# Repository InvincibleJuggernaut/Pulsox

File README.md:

<h2>Introduction</h2>

<p> Pulse oximeters are electronic devices capable of measuring blood oxygen concentration levels as well as heart beat rate. Although they originally found their use only in medical institutions, the COVID-19 pandemic led to rise in demand for such devices. Naturally, prices shot up through the roof with people being forced to buy them at 3-4x the prices to save their dear ones' lives. </p>
<p> Pulsox is an IoT based pulse oximeter capable of detecting heart rate as well as oxygen concentration. The data is displayed locally in the LCD display as well as sent to the Blynk IoT platform. This data can be visualized in real-time through an app. 
  </p>

<h2>Installation</h2>

<p>Following are the steps related to usage and installation:</p>
<ul>
  <li>Once the circuit has been assembled with the <a href="https://github.com/InvincibleJuggernaut/Pulsox#components">components</a> as shown <a href="https://github.com/InvincibleJuggernaut/Pulsox#schematic">here</a>, connect the microcontroller to the PC using a USB cable.</li>
  <li>Clone this repository using</li>
  
```
  git clone https://github.com/InvincibleJuggernaut/Pulsox.git
```
  <li>Open the file <i>pulsox.ino</i> using your preferred IDE and flash it to the microcontroller</li>
  <li>To observe the readings in the <a href="https://blynk.io/">Blynk</a> app, you first need to setup an account and paste the credentials along with the wireless network credentials inside the code in <i>pulsox.ino</i>. You could follow this <a href="https://www.electronicslovers.com/2018/06/esp8266-in-combination-with-blynk-app.html">tutorial</a>.</li> 
</ul>

<h2>Components</h2>

<ul>
  <li>NodeMCU ESP8266</li>
  <li>MAX30102</li>
  <li>LCD 16x2</li>
  </ul>
  
<h2>Schematic</h2>

<p align="center">
  <b>Circuit schematic</b>
  </p>
  
  <br>
  <br>
  
<h2>Layout</h2>

  <p align="center">
  <b>PCB layout for Pulsox</b>
</p>

<br>
<br>

<p align="center">
  <b>Real life rendering of PCB</b>
  </p>
  
  <br>
  <br>
  
<p><b>Note:</b> <i> Although the final circuit made use of MAX30102 as the pulse oximetry unit, the circuit schematic as well as the PCB design has been made using another pulse oximentry unit called as MAX30100 since there were no footprint libraries available for MAX30102. However, both the sensors are built by Maxim Integrated having similar functions and may only differ in physical dimensions.</i></p>

<h2>License</h2>

<a href="LICENSE">GPLv3</a>

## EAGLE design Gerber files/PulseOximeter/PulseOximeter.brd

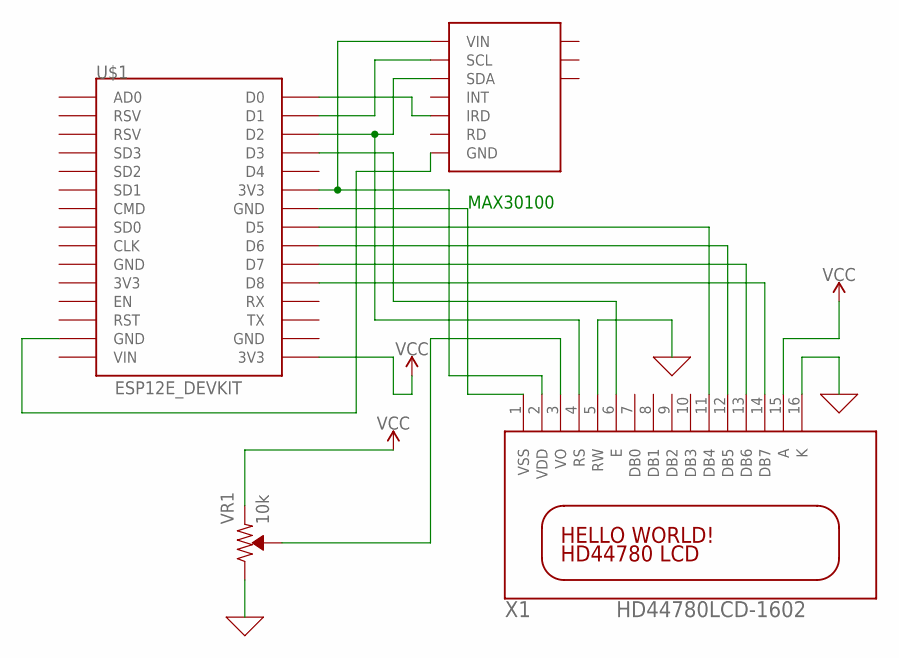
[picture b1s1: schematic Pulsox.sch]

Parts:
MAX30100: MAX30100
U$1: ESP12E_DEVKIT
VR1: 10k; TRIMPOT-PTH-3386U
X1: HD44780LCD-1602; LCD1602

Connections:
0: VR1.3 (CW), X1.5 (RW), X1.16 (K)
unnamed: MAX30100.3 (SCL), U$1.D1
unnamed: MAX30100.4 (SDA), U$1.D2, X1.4 (RS)
unnamed: MAX30100.6 (IRD), U$1.D0
unnamed: MAX30100.9 (GND), U$1.GND@1 (GND)
unnamed: U$1.D8, X1.14 (DB7)
unnamed: U$1.D7, X1.13 (DB6)
unnamed: U$1.D6, X1.12 (DB5)
unnamed: U$1.D5, X1.11 (DB4)
unnamed: U$1.D3, X1.6 (E)
unnamed: VR1.2 (WIPER), X1.3 (VO)
VCC: U$1.3V3@2 (3V3), VR1.1 (CCW), X1.15 (A)
VDD: MAX30100.2 (VIN), U$1.3V3@1 (3V3), X1.2 (VDD)
VSS: U$1.GND@2 (GND), X1.1 (VSS)

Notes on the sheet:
MAX30100

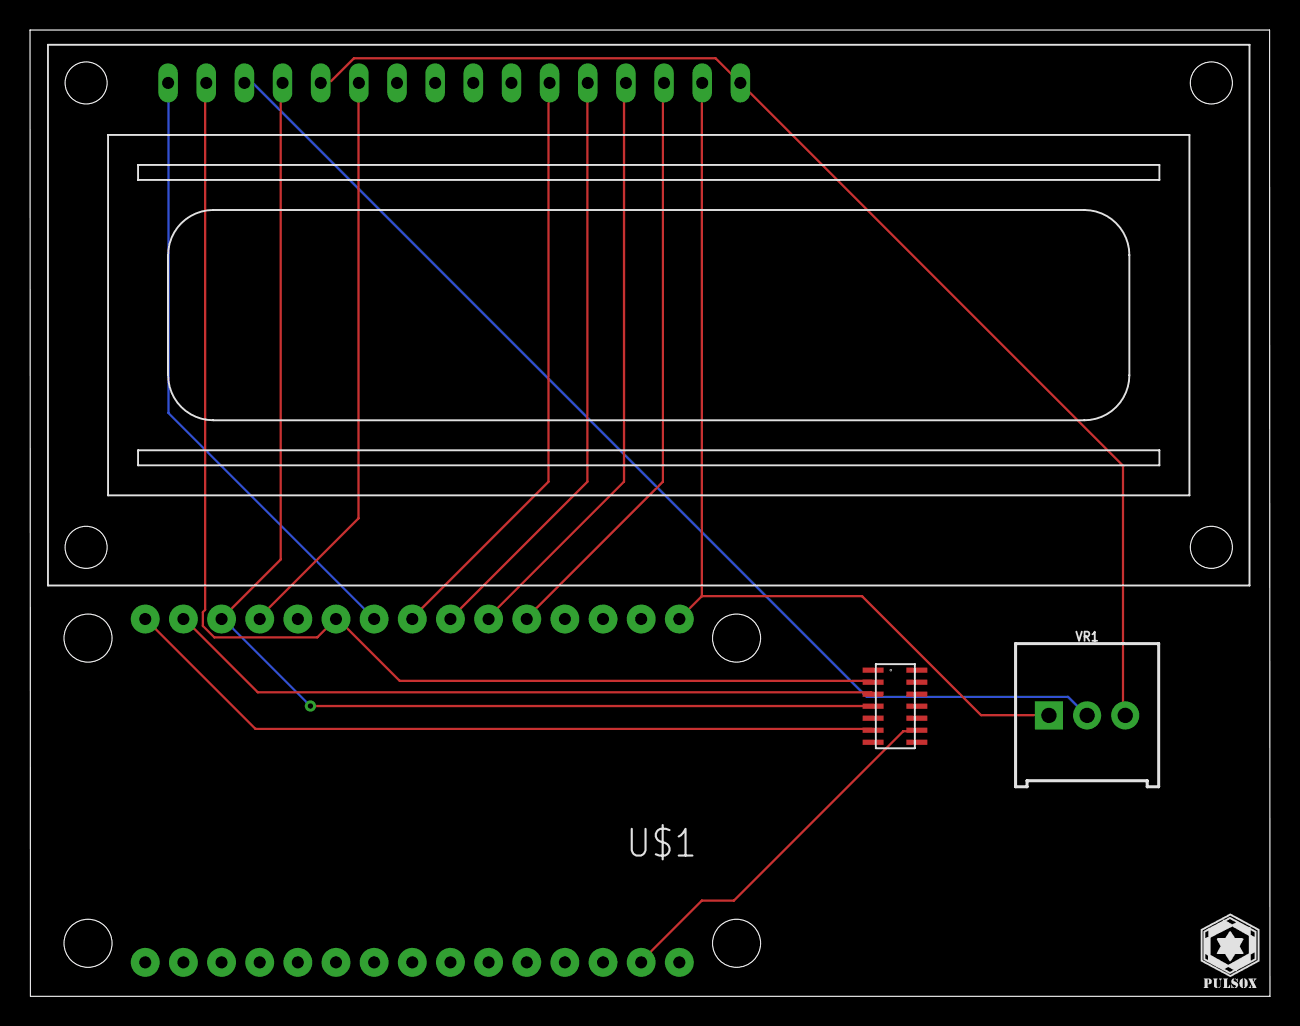
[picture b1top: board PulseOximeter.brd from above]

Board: 2 copper layers, 82.6 x 64.3 mm, 4 parts (0 on the bottom side), 14 nets.

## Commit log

2021-06-05 Gerber files
2021-06-29 Circuit schematic
2021-07-01 Create LICENSE
2021-07-03 Added instructions for usage

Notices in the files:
parts and their libraries:
SparkFun-Resistors: Licensing: Creative Commons ShareAlike 4.0 International - https://creativecommons.org/licenses/by-sa/4.0
